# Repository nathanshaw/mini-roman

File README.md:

# mini-roman
Repo to house the code, illustrator files, and other resources for the Mini Roman mechatronic sculpture.

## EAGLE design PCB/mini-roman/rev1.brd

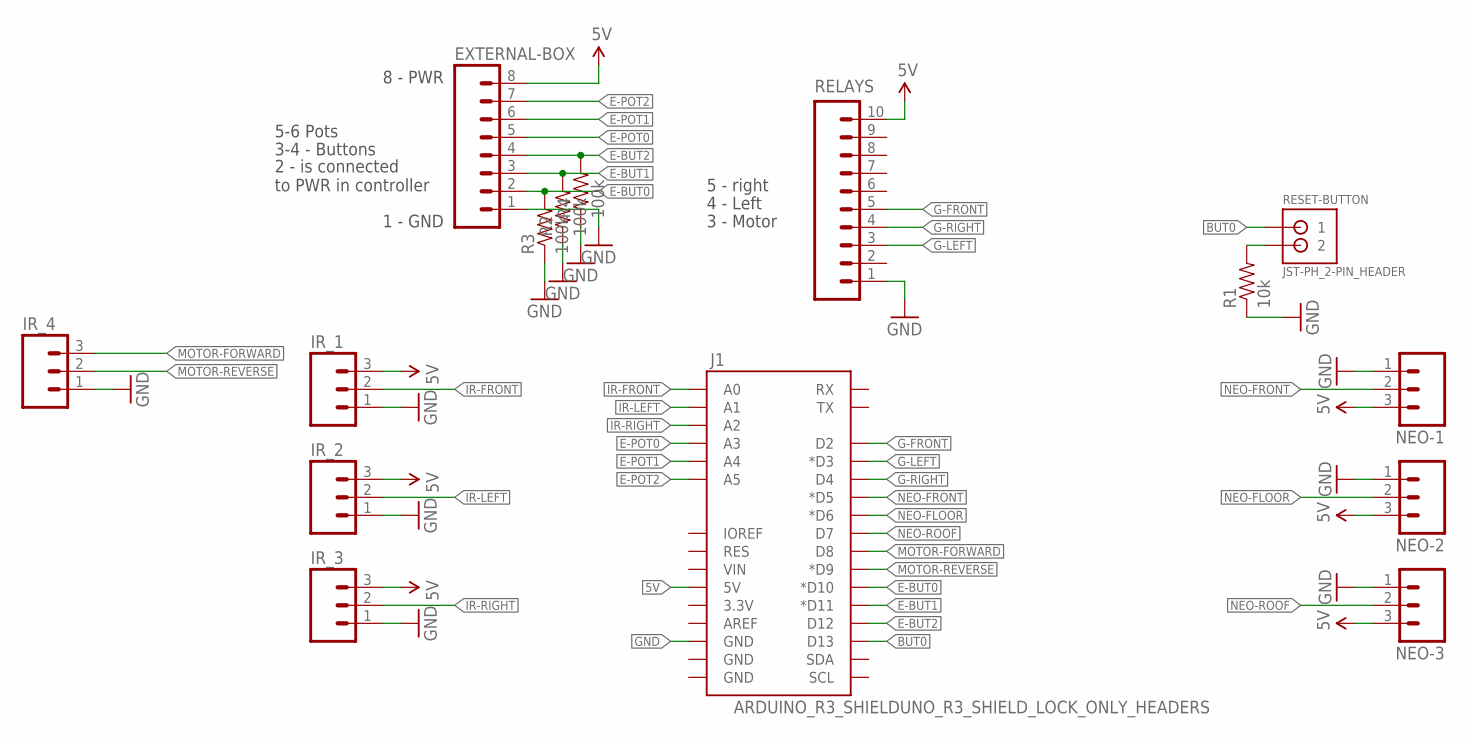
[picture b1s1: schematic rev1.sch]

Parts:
EXTERNAL-BOX: M08NO_SILK; 1X08_PIN1_NO_SILK
IR_1, IR_2, IR_3, IR_4: M03POLAR; MOLEX-1X3
J1: ARDUINO_R3_SHIELDUNO_R3_SHIELD_LOCK_ONLY_HEADERS; UNO_R3_SHIELD_ONLY_HEADERS
NEO-1, NEO-2, NEO-3: M03POLAR; MOLEX-1X3
R1: 10k; AXIAL-0.3
R2, R3, R4: 100k; AXIAL-0.3
RELAYS: M10NO_SILK_PTH_FEMALE; 1X10_NO_SILK
RESET-BUTTON: JST-PH_2-PIN_HEADER; JST_B2B-PH_HEADER

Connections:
5V: EXTERNAL-BOX.8, IR_1.3, IR_2.3, IR_3.3, J1.5V, NEO-1.3, NEO-2.3, NEO-3.3, RELAYS.10
BUT0: J1.D13, RESET-BUTTON.P1 (1)
E-BUT0: EXTERNAL-BOX.2, J1.D10 (*D10), R3.P$2 (2)
E-BUT1: EXTERNAL-BOX.3, J1.D11 (*D11), R2.P$2 (2)
E-BUT2: EXTERNAL-BOX.4, J1.D12, R4.P$2 (2)
E-POT0: EXTERNAL-BOX.5, J1.A3
E-POT1: EXTERNAL-BOX.6, J1.A4
E-POT2: EXTERNAL-BOX.7, J1.A5
G-FRONT: J1.D2, RELAYS.5
G-LEFT: J1.D3 (*D3), RELAYS.3
G-RIGHT: J1.D4, RELAYS.4
GND: EXTERNAL-BOX.1, IR_1.1, IR_2.1, IR_3.1, IR_4.1, J1.GND@2 (GND), NEO-1.1, NEO-2.1, NEO-3.1, R1.P$1 (1), R2.P$1 (1), R3.P$1 (1), R4.P$1 (1), RELAYS.1
IR-FRONT: IR_1.2, J1.A0
IR-LEFT: IR_2.2, J1.A1
IR-RIGHT: IR_3.2, J1.A2
MOTOR-FORWARD: IR_4.3, J1.D8
MOTOR-REVERSE: IR_4.2, J1.D9 (*D9)
unnamed: R1.P$2 (2), RESET-BUTTON.P2 (2)
NEO-FLOOR: J1.D6 (*D6), NEO-2.2
NEO-FRONT: J1.D5 (*D5), NEO-1.2
NEO-ROOF: J1.D7, NEO-3.2

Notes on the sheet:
1 - GND
8 - PWR
2 - is connected to PWR in controller
3-4 - Buttons
5-6 Pots
3 - Motor
4 - Left
5 - right

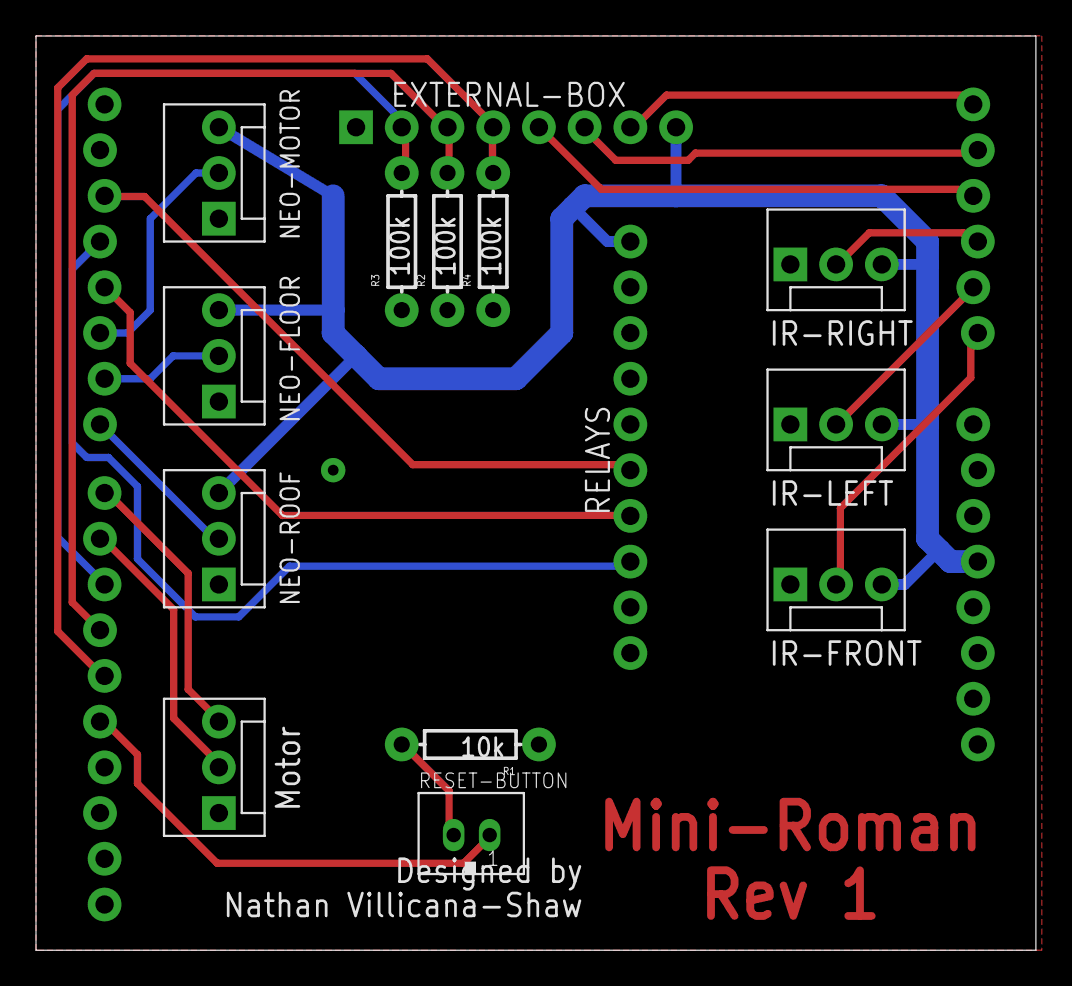
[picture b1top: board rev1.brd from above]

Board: 2 copper layers, 55.5 x 50.8 mm, 15 parts (0 on the bottom side), 21 nets.

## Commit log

2017-10-24 first real commit
2018-02-05 added the gerbers and EAGLE files for the PCB
2018-02-05 added all the illustrator files
2018-02-05 moved some files, and consolidated things into less files
2018-02-09 fixed bug in code which prevented the lights from turning white before the motor starts.
2018-02-10 got the code ready for the exhibit more or less

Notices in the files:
parts and their libraries:
SparkFun-Connectors: Licensing: Creative Commons ShareAlike 4.0 International - https://creativecommons.org/licenses/by-sa/4.0
